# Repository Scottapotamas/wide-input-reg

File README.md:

# Wide input (HV) DC Step-down Regulator
This is a smaller board that follows the successful design used on the zaphod-bot delta robot, which used 75VDC input and 12V output, tested at 4A load with 96% efficiency.

This board is intended as a medium scale (~50-100W) standalone version for use with 12S lipo systems (48Vish) and similar high voltage supplies, as its hard to get a high input voltage regulator from Pololu etc.

## Design Notes

### Regulator

Uses a TI regulator, and a reasonably chunky inductor/filtering stage to ensure stability and efficiency. This design isn't designed for low cost, as I don't forsee low runs, and high voltage systems which require a board like this aren't typically cheap to begin with.

While the regulator and most parts are capable of 100VDC inputs, I've intended the maximum input voltage to be around 80VDC, and I'd expect the design to be used for 5, 12, or 24V outputs (though other outputs are achievable with some component changes).

### Sensing and feedback

Onboard output voltage and current sensing is achieved with the INA219 I2C sense IC, which allows the output voltage and current to be accurately reported to a host microcontroller.

Regulator provides some minimal status indication with 2 leds mounted near the input connector: 

- Red LED indicates the presence of input voltage, and the 

- Green LED indicates the presence of an output voltage. 

- These LED's are 'dumb' and do not indicate if the input/output voltages are _correct_.

A series of onboard solder link jumpers are used to set the I2C address of the INA219, for systems which use multiple regulator boards for different logic levels.

### Connectors

- Input power connection with Molex Sabre 2-pin connector, output with Molex Minifit 4-pin. 

- Data is a JST-GH locking 6-pin connector, which should provide 3.3V, and I2C from the host system. 
  - An (optionally connected) 3.3V analog signal provides input voltage sensing for an ADC, with a 27:1 divider.

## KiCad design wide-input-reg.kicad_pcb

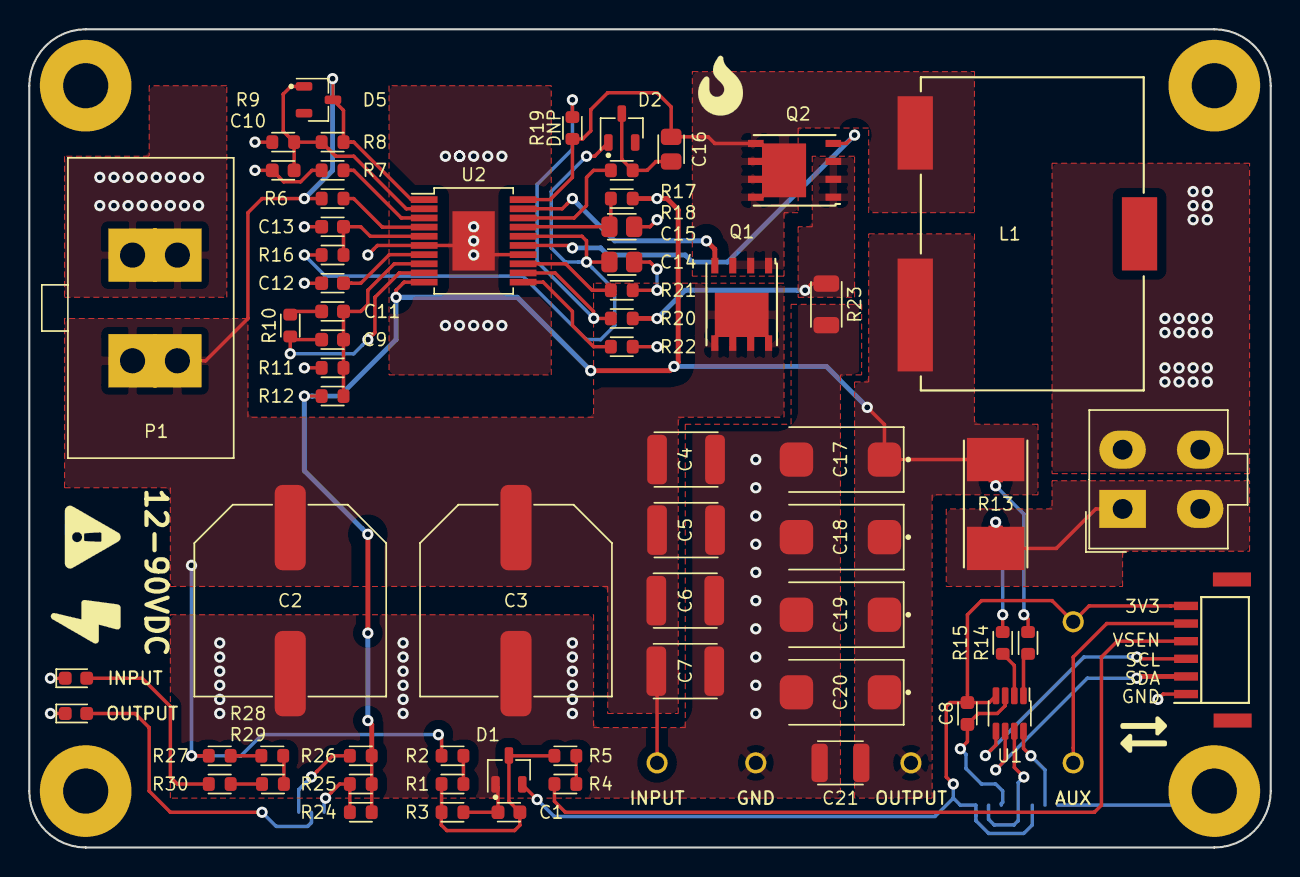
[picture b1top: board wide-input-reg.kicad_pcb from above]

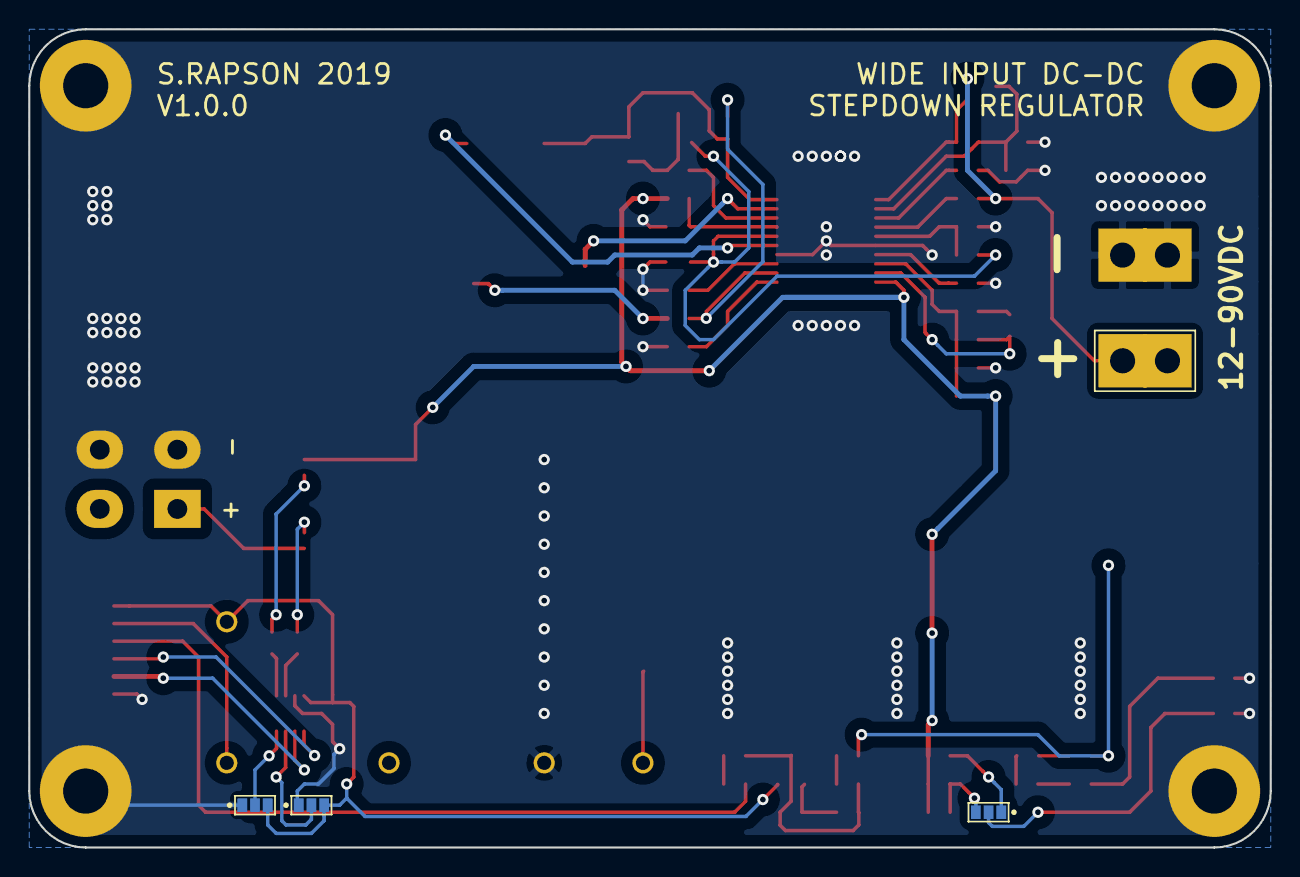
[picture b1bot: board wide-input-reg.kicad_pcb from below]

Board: 2 copper layers, 88.0 x 58.0 mm, 80 parts (3 on the bottom side), 44 nets.

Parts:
C1, C8, C12: 100n_X7R_1608M; CAPC1608X90N
C2, C3: 47u_ELEC_100V_1350X1350M; CAPAE1350X1350D1490DD450L470N
C4, C5, C6, C7: 2u2_X7R_4532M; CAPC4532X180N
C9: 15p_X7R_1608M; CAPC1608X90N
C10: 1u_X7R_1608M; CAPC1608X90N
C11: 1n5_X7R_1608M; CAPC1608X90N
C13: 330p_X7R_1608M; CAPC1608X90N
C14, C15, C16: 1u_X7R_2012M; CAPC2012X110N
C17, C18, C19, C20: 47u_TANT_7343M; CAPPM7343X310N
C21: 22u_X7R_3225M; CAPC3225X170N
D1: BAV99; SOT95P240X110-3L16N
D2, D5: 200V_350mW_SOT23; SOT95P240X110-3L16N
D3: LED_RED_1608M; LEDC1608X80L40N
D4: LED_GREEN_1608M; LEDC1608X80L40N
L1: 10u2_PA2050; PULSE_PA2050
LOGO1: LOGO; BOLT_LOGO_310X490
LOGO2: LOGO; WARN_TRIANGLE_LOGO440X400
LOGO3: LOGO; FIRE_LOGO_320X420
LOGO4: LOGO; DUPLEX_LOGO330X260
MNT1, MNT2, MNT3, MNT4: MNT_M3_PLATED; MTGP650H330
P1: MOLEX_43160-0102; Molex_Sabre_43160-0102_VERT
P2: JST_GH_6_RA; SM06B-GHS-TB
P3: MOLEX_MINIFIT_JR_2x2_WAY; Molex_Mini-Fit_Jr_5566-04A_2x02_P4.20mm_Vertical
Q1, Q2: Si7852DP; SON127P490X575X90-9T313X381M
R1, R2: 130K_1608M; RESC1608X50N
R3, R22, R24, R25: 10K0_1608M; RESC1608X50N
R4, R19, R20, R21: 0R_1608M; RESC1608X50N
R5, R14, R15: 1K00_1608M; RESC1608X50N
R6: 1M_1608M; RESC1608X50N
R7: 12K7_1608M; RESC1608X50N
R8: 102K_1608M; RESC1608X50N
R9: 9K53_1608M; RESC1608X50N
R10: 39K_1608M; RESC1608X50N
R11: 1K2_1608M; RESC1608X50N
R12: 10K7_1608M; RESC1608X50N
R13: R005_METAL_SHUNT; OARS1-R005FI
R16: 750K_1608M; RESC1608X50N
R17: 2R2_1608M; RESC1608X50N
R18: 1R0_1608M; RESC1608X50N
R23: R01_3216M; RESC3216X140N
R26, R27, R28, R29, R30: 2K40_1608M; RESC1608X50N
SL1, SL2, SL3: SOLDER-LINK-3; SJ1608-3N
TEST1: CLIP_HOOK_BROWN; KEYSTONE_5115
TEST2: CLIP_HOOK_YELLOW; KEYSTONE_5004
TEST3: CLIP_HOOK_WHITE; KEYSTONE_5002
TEST4: CLIP_HOOK_ORANGE; KEYSTONE_5003
TEST5: CLIP_HOOK_BLACK; KEYSTONE_5001
U1: INA219AID**; SOT23-8P65_280X145L45X30N
U2: LM5116; SOP21P65_720X780X200L75X30N

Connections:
+3.3V: C8.2, D1.2, P2.6, SL2.3, SL3.3, TEST4.1, U1.4
+BATT: C2.1, C3.1, C4.1, C5.1, C6.1, C7.1, D5.3, P1.1, Q1.3, R1.2, R6.2, R8.1, R27.2, TEST1.1, U2.1
+POWER: C17.1, C18.1, C19.1, C20.1, C21.1, L1.2, R12.1, R13.1, R18.1, R24.2, R25.2, R26.2, TEST2.1, U2.10
/SUPPLY: P3.1, P3.3, R13.2
GND: C1.2, C2.2, C3.2, C4.2, C5.2, C6.2, C7.2, C8.1, C10.1, C12.2, C13.2, C14.1, C15.1, C17.2, C18.2, C19.2, C20.2, C21.2, D1.1, D3.C, D4.C, MNT1.1, MNT2.1, MNT3.1, MNT4.1, P1.2, P2.1, P3.2, P3.4, R3.1, R7.1, R9.2, R11.2, R21.1, R22.1, R23.2, SL2.1, SL3.1, TEST5.1, U1.3, U2.6, U2.14, U2.EP
unnamed: C1.1, D1.3, R2.1, R3.2, R5.2
unnamed: C9.1, R10.1, U2.9
unnamed: C10.2, D5.1, R8.2, R9.1, U2.2
unnamed: C9.2, C11.1, R11.1, R12.2, U2.8
unnamed: C11.2, R10.2
unnamed: C12.1, U2.7
unnamed: C13.1, R16.2, U2.5
unnamed: C14.2, D2.1, R16.1, U2.16
unnamed: C15.2, R18.2, U2.17
unnamed: C16.1, L1.1, Q1.2, Q2.3, R19.1, U2.20
unnamed: C16.2, D2.3, R17.2
unnamed: D3.A, R30.1
unnamed: D4.A, SL1.2
unnamed: P2.4, R4.1
unnamed: P2.5, TEST3.1
unnamed: Q1.1, U2.19
unnamed: Q2.1, U2.15
unnamed: Q2.2, R20.1, R23.1
unnamed: R1.1, R2.2
unnamed: R6.1, U2.4
unnamed: R7.2, U2.3
unnamed: R13.3, R14.2
unnamed: R13.4, R15.1
unnamed: R14.1, U1.1
unnamed: R15.2, U1.2
unnamed: R17.1, U2.18
unnamed: R19.2, R20.2, U2.12
unnamed: R21.2, U2.13
unnamed: R22.2, U2.11
unnamed: R24.1, R25.1, SL1.3
unnamed: R26.1, SL1.1
unnamed: R27.1, R29.2
unnamed: R28.1, R30.2
unnamed: R28.2, R29.1
unnamed: SL2.2, U1.7
unnamed: SL3.2, U1.8
SCL: P2.3, U1.5
SDA: P2.2, U1.6
VOLTAGE_INPUT: R4.2, R5.1

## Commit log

2018-11-13 Moved current project files into repo.
    Schematic base is complete(ish) and some very preliminary parts layout has started.
2018-11-13 Building out the readme with design notes
2018-11-13 Minor readme formatting changes
2018-11-23 Parts placement
2018-11-23 Routing and copper pours
2018-11-23 Routing, Silkscreen, pour tweaks, etc
    Generally progressing towards completion
2019-04-04 Silkscreen text, finished remaining tracks, etc
    Ready for fab
2019-04-04 Adds gerbers and PDF exports
2019-04-04 Adds rendered views of PCB
2019-04-04 Minor readme tweaks
2019-04-04 Render embedded in readme
